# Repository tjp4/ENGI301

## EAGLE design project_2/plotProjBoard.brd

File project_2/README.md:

README

Project 02 contains the board and schematics for the plotter project made in project 01.

plotProjBoard.brd is the final version of the PCB, and uses the PocketBeagle, 2 DRV8833s, a 2.1mm Power Jack, and and a 3 pin 90 deg header. 

Associated documents are contained in the docs folder, including the BOM, gerber views, proposal, and schematic pdf.

-Tyler Pitts, ENGI301

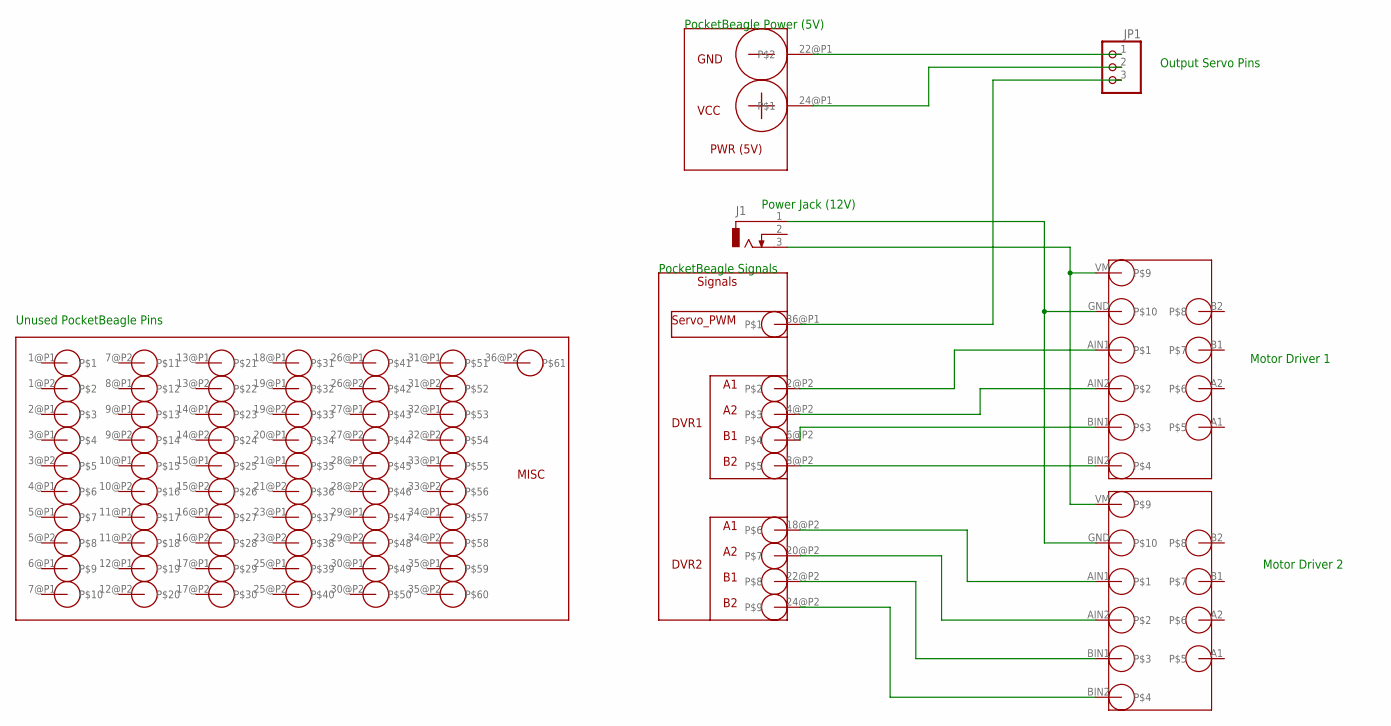
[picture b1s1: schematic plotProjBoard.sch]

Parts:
J1: DCJ0303
JP1: SERVO/90; 1X03/90
U$1, U$3: DRV8833
U$2: POCKETBEAGLE

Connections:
unnamed: U$1.AIN1, U$2.2@P2
unnamed: U$1.AIN2, U$2.4@P2
unnamed: U$1.BIN1, U$2.6@P2
unnamed: U$1.BIN2, U$2.8@P2
unnamed: U$2.18@P2, U$3.AIN1
unnamed: U$2.20@P2, U$3.AIN2
unnamed: U$2.22@P2, U$3.BIN1
unnamed: U$2.24@P2, U$3.BIN2
unnamed: JP1.3, U$2.36@P1
unnamed: JP1.2, U$2.24@P1
unnamed: JP1.1, U$2.22@P1
unnamed: J1.1, U$1.GND, U$3.GND
unnamed: J1.3, U$1.VM, U$3.VM

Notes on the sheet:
Unused PocketBeagle Pins
PocketBeagle Power (5V)
Power Jack (12V)
PocketBeagle Signals
Motor Driver 1
Motor Driver 2
Output Servo Pins

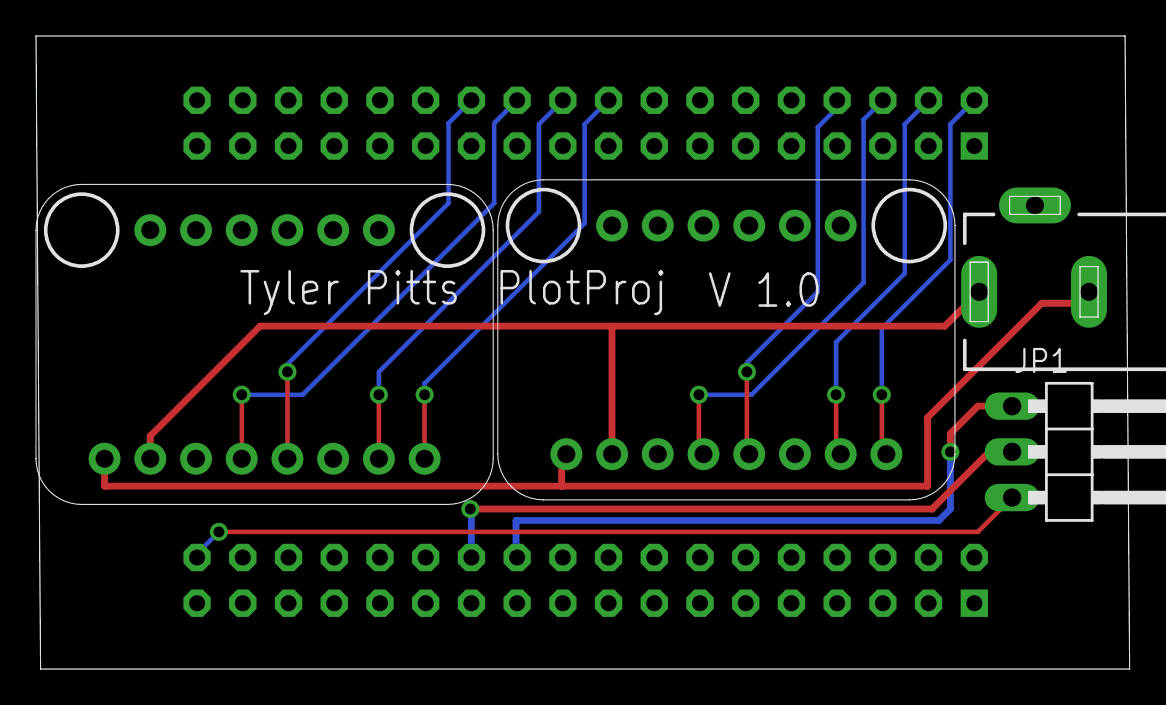
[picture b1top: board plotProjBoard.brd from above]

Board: 2 copper layers, 60.8 x 35.2 mm, 5 parts (1 on the bottom side), 13 nets.

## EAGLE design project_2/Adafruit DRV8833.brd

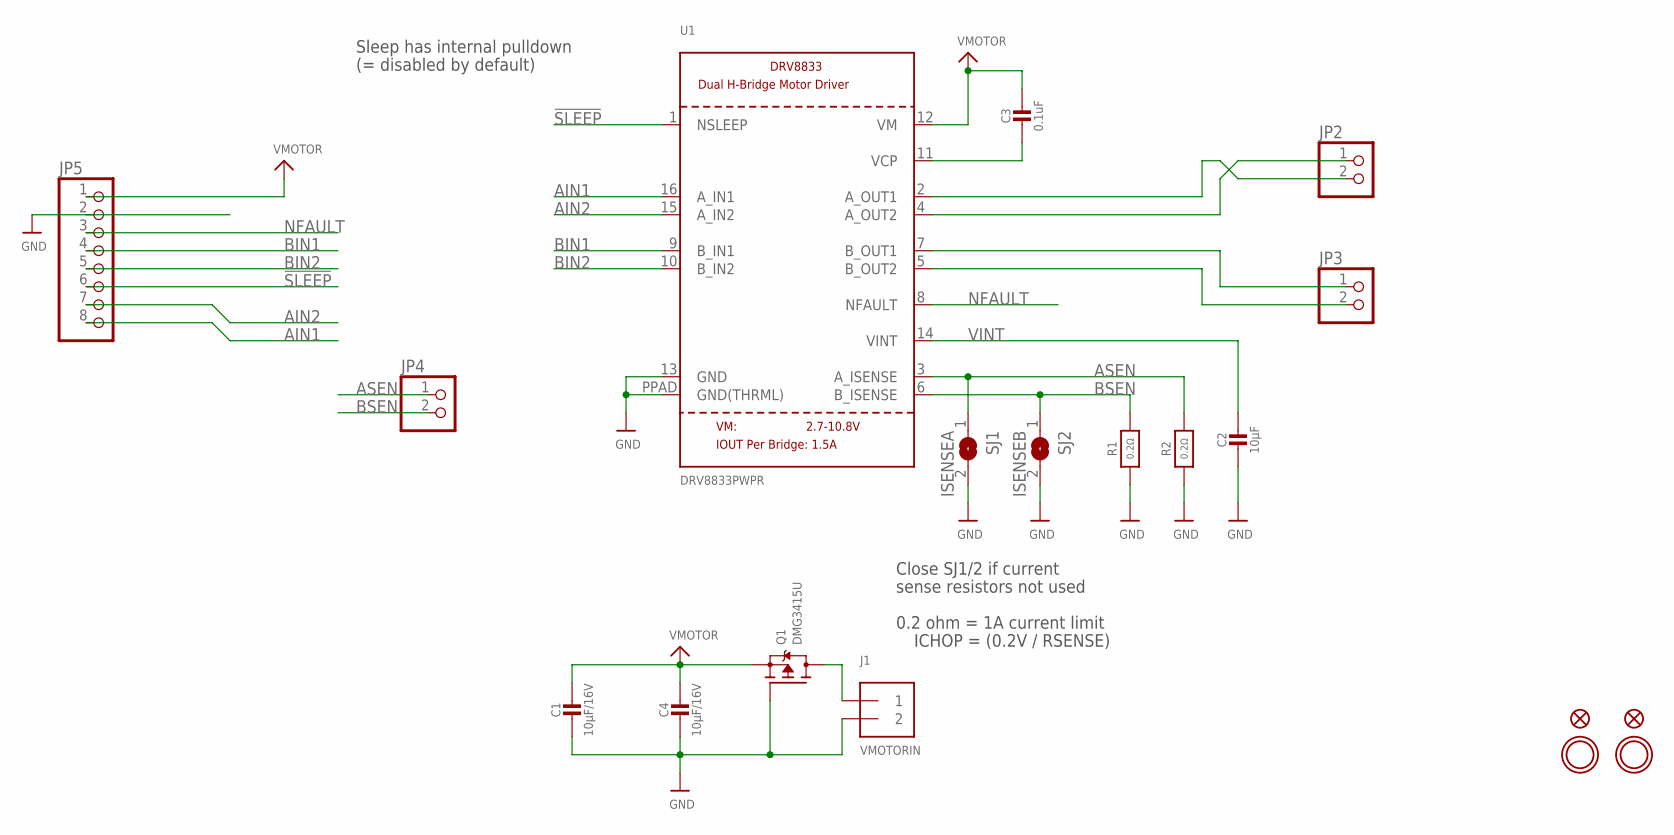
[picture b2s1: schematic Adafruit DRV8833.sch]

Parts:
C1, C4: 10µF/16V; 0805-NO
C2: 10µF; 0805-NO
C3: 0.1uF; 0805-NO
FID1, FID2: FIDUCIAL""; FIDUCIAL_1MM
J1: VMOTORIN; TERMBLOCK_1X2-3.5MM
JP2, JP3, JP4: HEADER-1X2ROUND; 1X02_ROUND
JP5: HEADER-1X870MIL; 1X08_ROUND_70
Q1: DMG3415U; SOT23-WIDE
R1, R2: 0.2Ω; _1206
SJ1: ISENSEA; SOLDERJUMPER_ARROW_NOPASTE
SJ2: ISENSEB; SOLDERJUMPER_ARROW_NOPASTE
U1: DRV8833PWPR; HTSSOP16
U$13, U$14: MOUNTINGHOLE2.5; MOUNTINGHOLE_2.5_PLATED

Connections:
!SLEEP: JP5.6, U1.1 (NSLEEP)
AIN1: JP5.8, U1.16 (A_IN1)
AIN2: JP5.7, U1.15 (A_IN2)
AOUT1: JP2.2, U1.2 (A_OUT1)
AOUT2: JP2.1, U1.4 (A_OUT2)
ASEN: JP4.1, R2.2, SJ1.1, U1.3 (A_ISENSE)
BIN1: JP5.4, U1.9 (B_IN1)
BIN2: JP5.5, U1.10 (B_IN2)
BOUT1: JP3.1, U1.7 (B_OUT1)
BOUT2: JP3.2, U1.5 (B_OUT2)
BSEN: JP4.2, R1.2, SJ2.1, U1.6 (B_ISENSE)
GND: C1.2, C2.2, C4.2, J1.2, JP5.2, Q1.1 (G), R1.1, R2.1, SJ1.2, SJ2.2, U1.13 (GND), U1.PPAD (GND(THRML))
unnamed: C3.2, U1.11 (VCP)
NFAULT: JP5.3, U1.8 (NFAULT)
PWRIN: J1.1, Q1.3 (D)
VINT: C2.1, U1.14 (VINT)
VMOTOR: C1.1, C3.1, C4.1, JP5.1, Q1.2 (S), U1.12 (VM)

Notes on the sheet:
Close SJ1/2 if current
sense resistors not used
0.2 ohm = 1A current limit
ICHOP = (0.2V / RSENSE)
Sleep has internal pulldown
(= disabled by default)

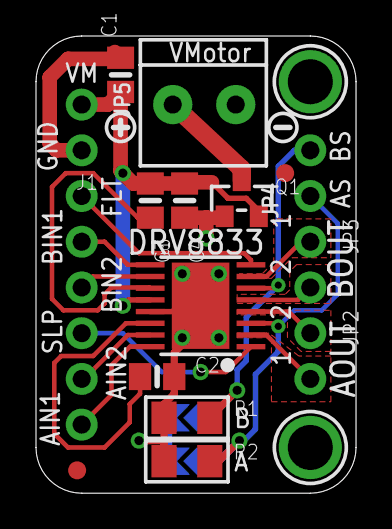
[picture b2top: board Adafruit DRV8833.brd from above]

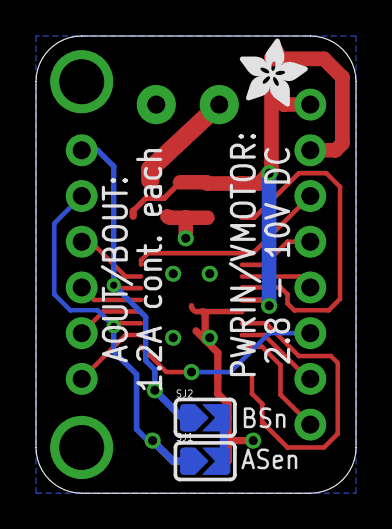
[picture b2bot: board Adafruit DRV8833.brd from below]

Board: 2 copper layers, 17.8 x 25.4 mm, 22 parts (3 on the bottom side), 17 nets.

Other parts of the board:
U$15: SYMBOL_PLUS
U$16: SYMBOL_MINUS
U$17: ADAFRUIT_3.5MM

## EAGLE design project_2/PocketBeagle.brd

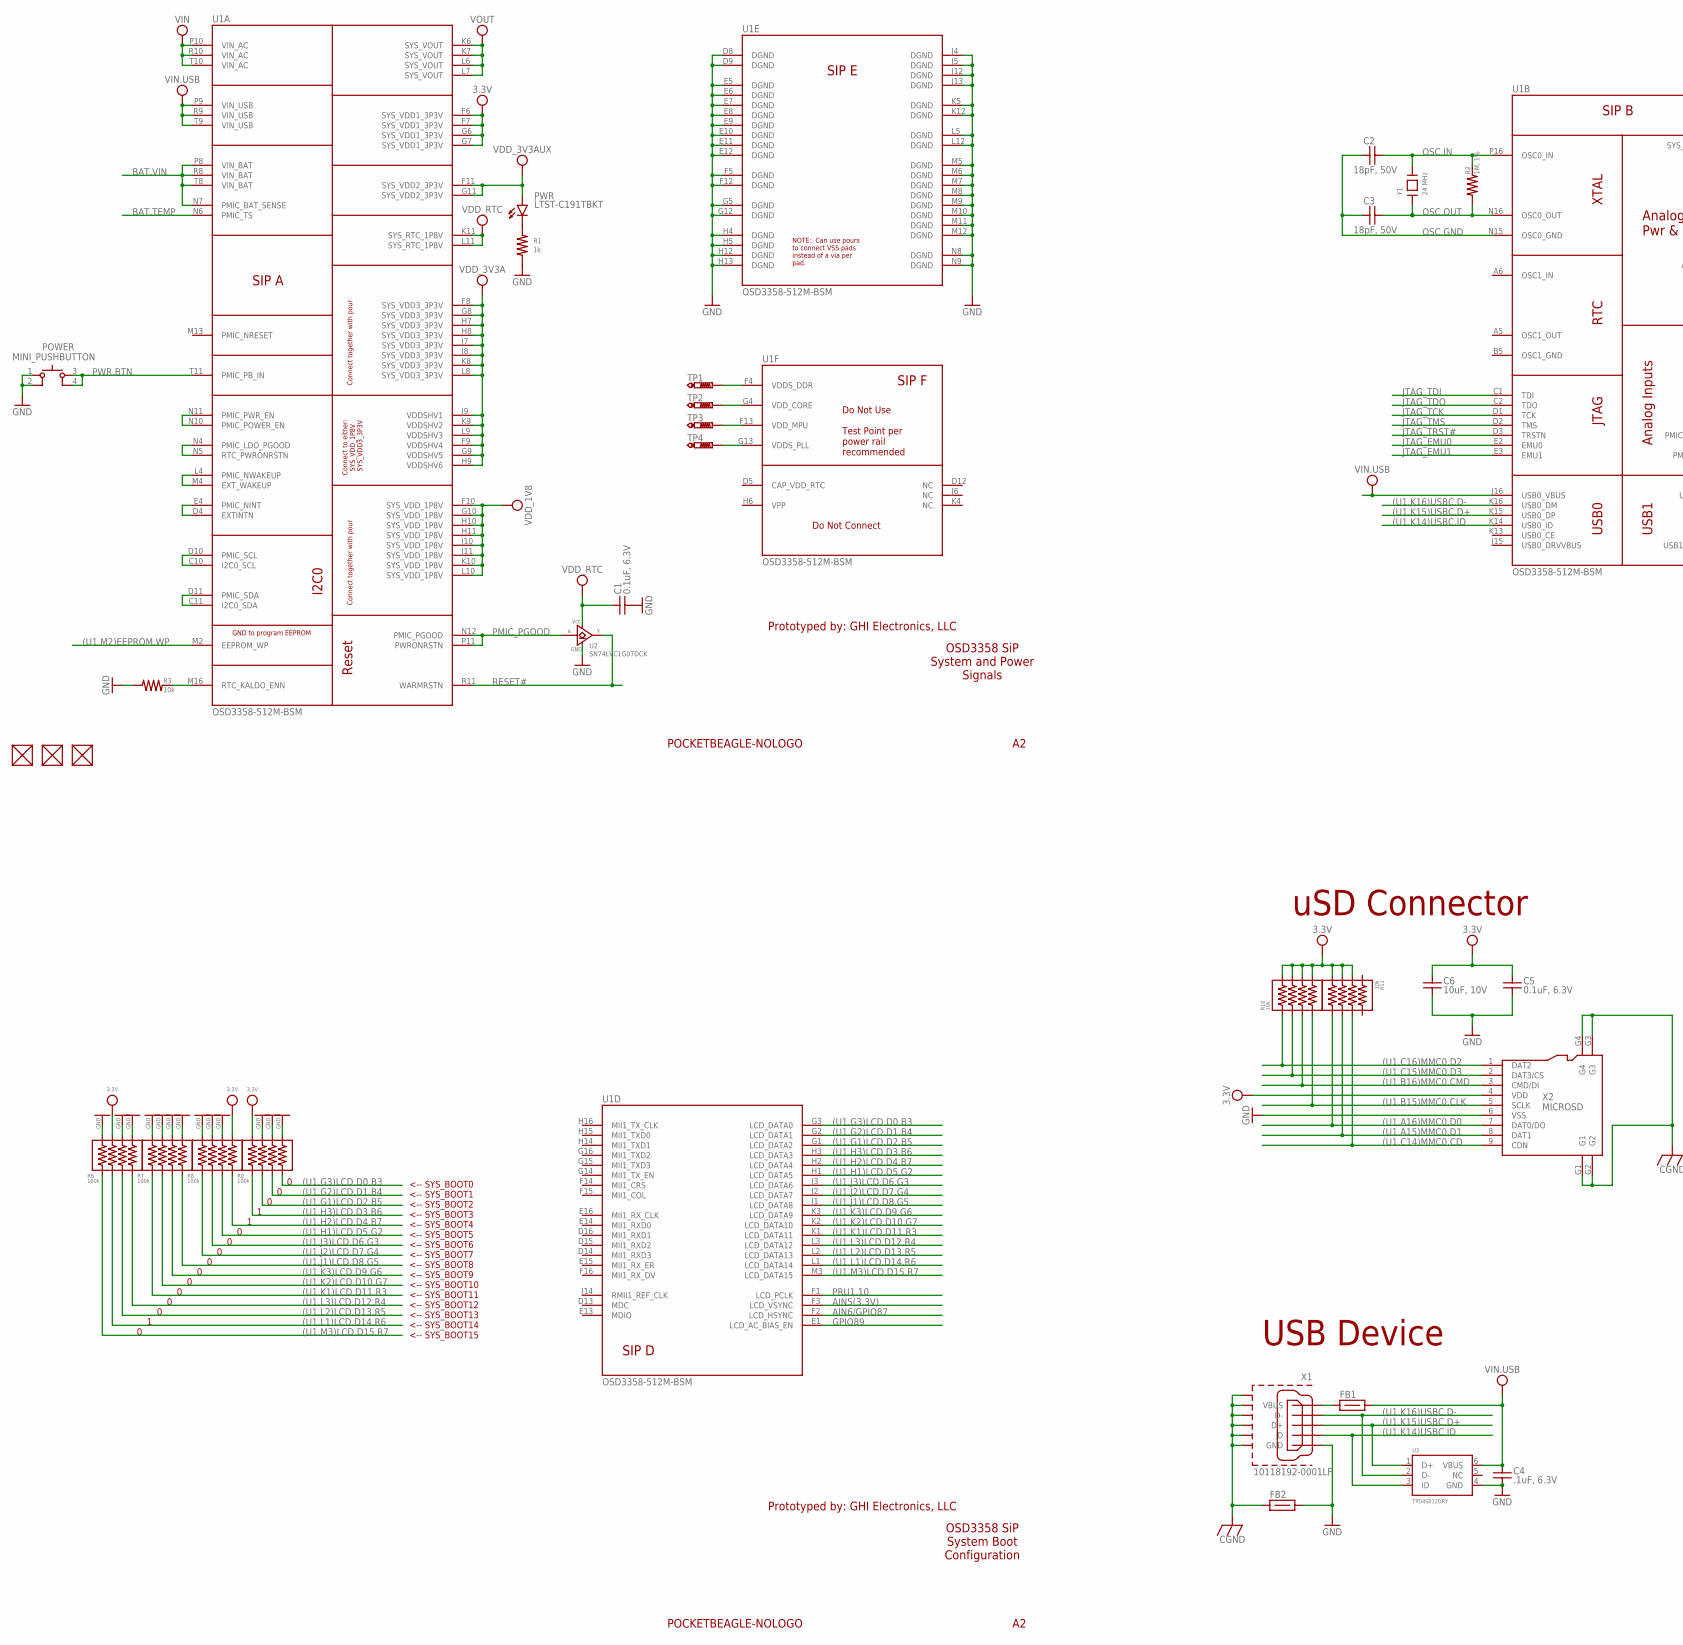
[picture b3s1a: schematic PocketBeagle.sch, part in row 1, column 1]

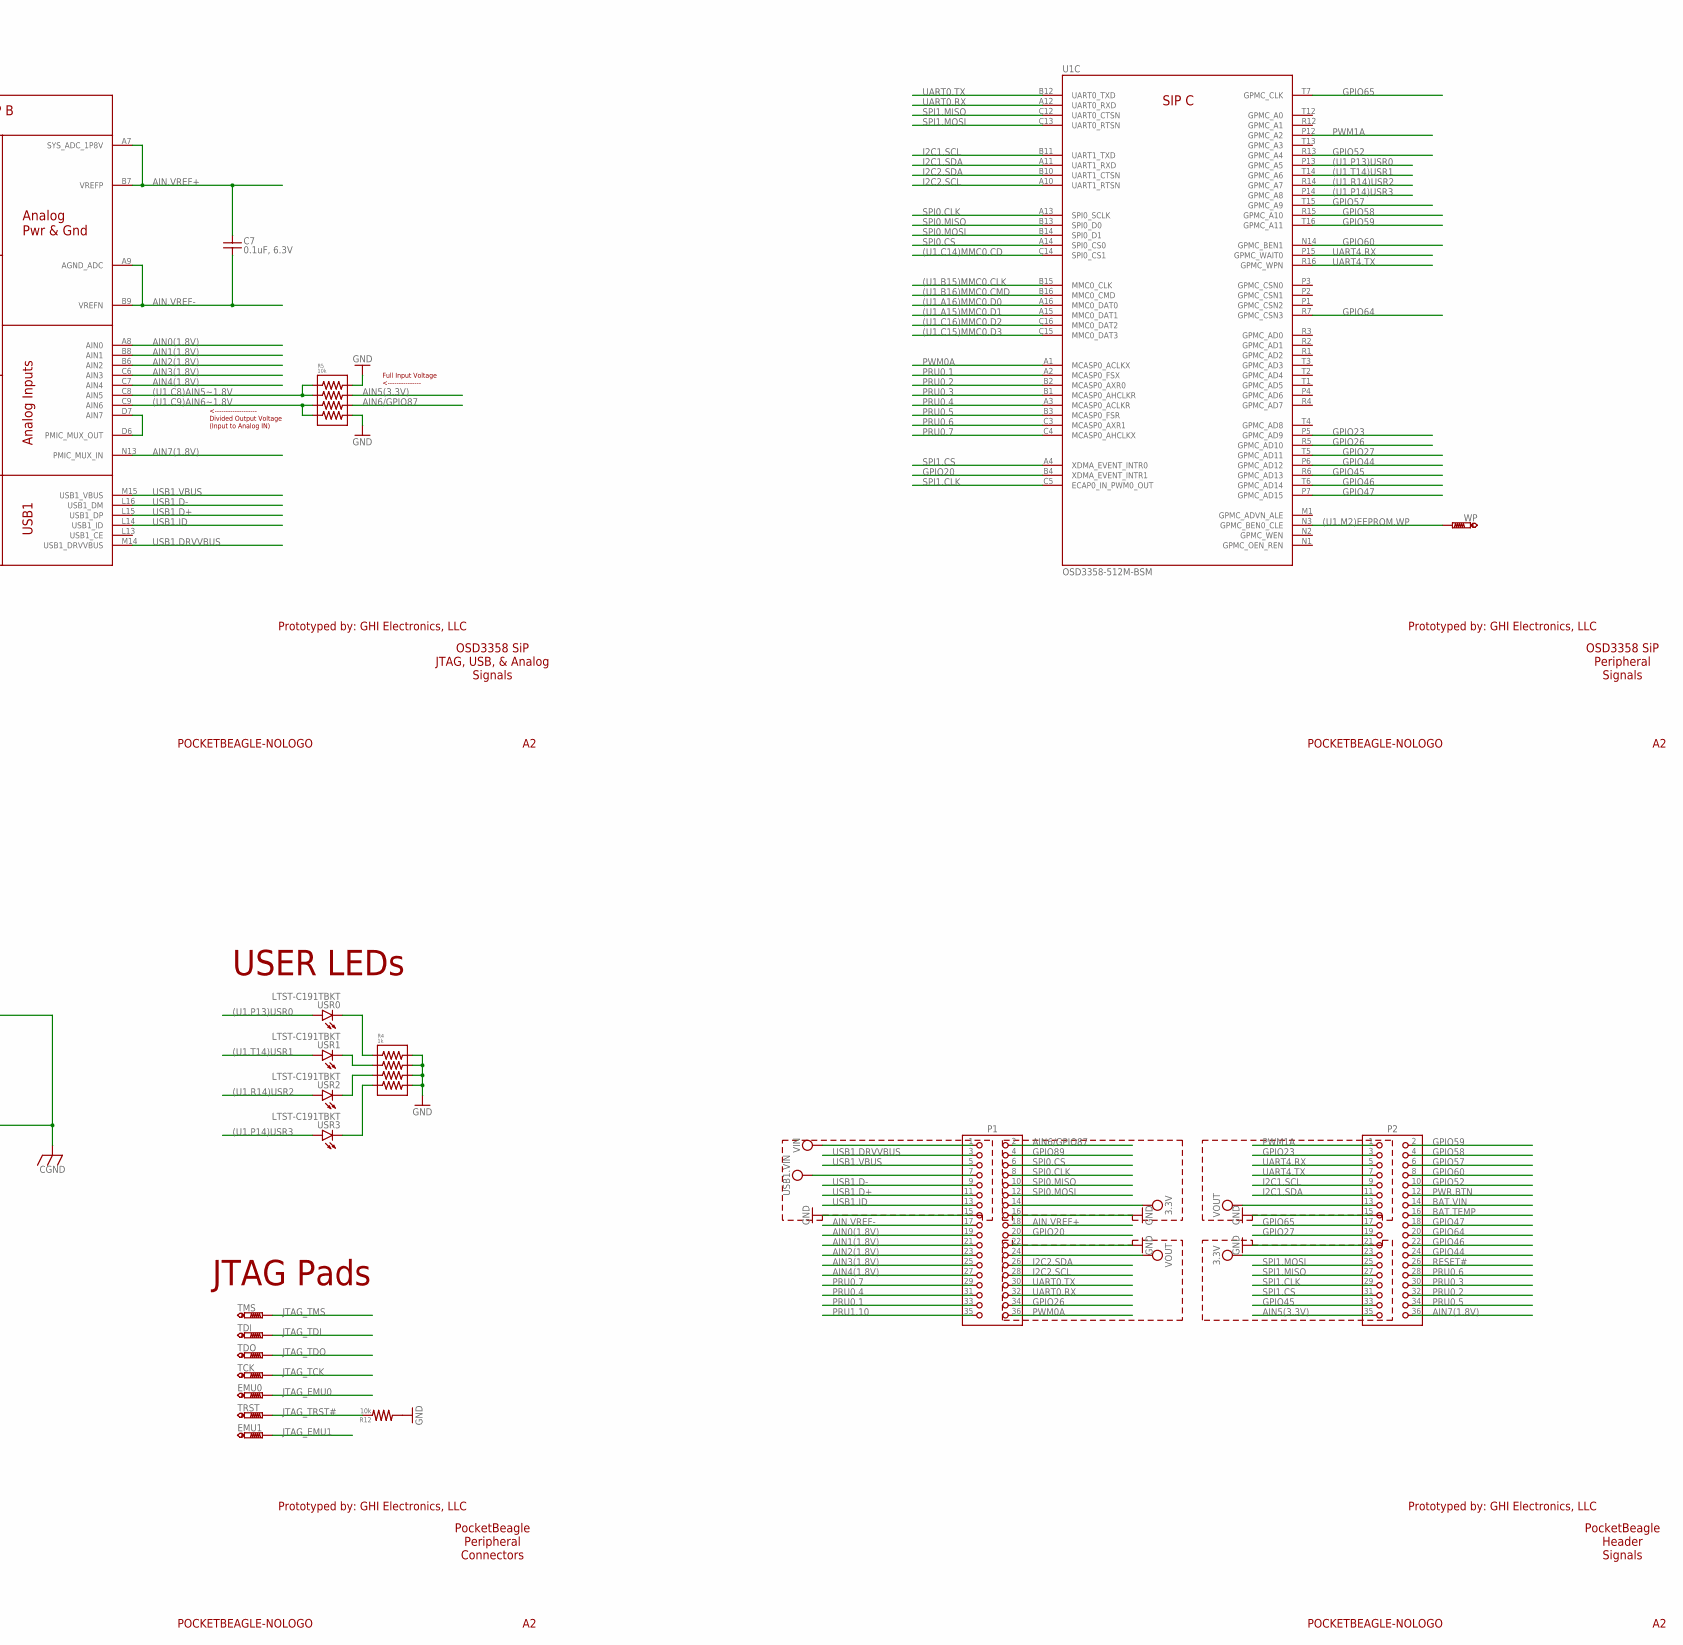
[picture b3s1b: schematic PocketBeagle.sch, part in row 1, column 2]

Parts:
C1, C5, C7: 0.1uF, 6.3V; 0402
C2, C3: 18pF, 50V; 0402
C4: .1uF, 6.3V; 0402
C6: 10uF, 10V; 0603
EMU0, EMU1: PTR1B1,27; B1,27
FB1, FB2: FB-(INCH)-0603; 0603
FUD1, FUD2, FUD3: FIDUCIAL; FIDUCIAL_40MIL
P1, P2: 2X18-(INCH)-0.1-TH-(35MIL-DIA)-W/O-SILK; TH-2X18-(35MIL-DIA)-W/O-SILK
POWER: MINI_PUSHBUTTON
PWR: LTST-C191TBKT; 0603-LED
R1: 1k; 0402
R2: 1M, 1%; 0402
R3, R12: 10k; 0402
R4: 1k; RN0804
R5, R10, R11: 10k; RN0804
R6, R7, R8, R9: 100k; RN0804
TCK: PTR1B1,27; B1,27
TDI: PTR1B1,27; B1,27
TDO: PTR1B1,27; B1,27
TMS: PTR1B1,27; B1,27
TP1, TP2, TP3, TP4: PTR1B1,27; B1,27
TRST: PTR1B1,27; B1,27
U1: OSD3358-512M-BSM; OSD335X-BGA-256
U2: SN74LVC1G07DCK; SC70(TI-DCK)
U3: TPD4S012DRY; SON-6(TI)-DRY
USR0, USR1, USR2, USR3: LTST-C191TBKT; 0603-LED
WP: PTR1B1,27; B1,27
X1: 10118192-0001LF; 10118192-0001LF(MICRO-USB-B-AMPHENOL-FCI)
X2: MICROSD
Y1: 24 MHz; CRYSTAL_5X3.2MM

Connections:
3.3V: C5.1, C6.1, P1.14, P2.23, R6.7, R8.5, R9.4, R10.5, R10.6, R10.7, R10.8, R11.2, R11.3, R11.4, U1.F6 (SYS_VDD1_3P3V), U1.F7 (SYS_VDD1_3P3V), U1.G6 (SYS_VDD1_3P3V), U1.G7 (SYS_VDD1_3P3V), X2.4 (VDD)
(U1.A15)MMC0.D1: R11.6, U1.A15 (MMC0_DAT1), X2.8 (DAT1)
(U1.A16)MMC0.D0: R11.5, U1.A16 (MMC0_DAT0), X2.7 (DAT0/DO)
(U1.B15)MMC0.CLK: R10.4, U1.B15 (MMC0_CLK), X2.5 (SCLK)
(U1.B16)MMC0.CMD: R10.3, U1.B16 (MMC0_CMD), X2.3 (CMD/DI)
(U1.C8)AIN5~1.8V: R5.1, R5.2, U1.C8 (AIN5)
(U1.C9)AIN6~1.8V: R5.3, R5.4, U1.C9 (AIN6)
(U1.C14)MMC0.CD: R11.7, U1.C14 (SPI0_CS1), X2.9 (CDN)
(U1.C15)MMC0.D3: R10.2, U1.C15 (MMC0_DAT3), X2.2 (DAT3/CS)
(U1.C16)MMC0.D2: R10.1, U1.C16 (MMC0_DAT2), X2.1 (DAT2)
(U1.G1)LCD.D2.B5: R9.6, U1.G1 (LCD_DATA2)
(U1.G2)LCD.D1.B4: R9.7, U1.G2 (LCD_DATA1)
(U1.G3)LCD.D0.B3: R9.8, U1.G3 (LCD_DATA0)
(U1.H1)LCD.D5.G2: R8.3, U1.H1 (LCD_DATA5)
(U1.H2)LCD.D4.B7: R8.4, U1.H2 (LCD_DATA4)
(U1.H3)LCD.D3.B6: R9.5, U1.H3 (LCD_DATA3)
(U1.J1)LCD.D8.G5: R7.4, U1.J1 (LCD_DATA8)
(U1.J2)LCD.D7.G4: R8.1, U1.J2 (LCD_DATA7)
(U1.J3)LCD.D6.G3: R8.2, U1.J3 (LCD_DATA6)
(U1.K1)LCD.D11.R3: R7.1, U1.K1 (LCD_DATA11)
(U1.K2)LCD.D10.G7: R7.2, U1.K2 (LCD_DATA10)
(U1.K3)LCD.D9.G6: R7.3, U1.K3 (LCD_DATA9)
(U1.K14)USBC.ID: U1.K14 (USB0_ID), U3.3 (ID), X1.ID
(U1.K15)USBC.D+: U1.K15 (USB0_DP), U3.1 (D+), X1.D+
(U1.K16)USBC.D-: U1.K16 (USB0_DM), U3.2 (D-), X1.D-
(U1.L1)LCD.D14.R6: R6.2, U1.L1 (LCD_DATA14)
(U1.L2)LCD.D13.R5: R6.3, U1.L2 (LCD_DATA13)
(U1.L3)LCD.D12.R4: R6.4, U1.L3 (LCD_DATA12)
(U1.M2)EEPROM.WP: U1.M2 (EEPROM_WP), U1.N3 (GPMC_BEN0_CLE), WP.TP
(U1.M3)LCD.D15.R7: R6.1, U1.M3 (LCD_DATA15)
(U1.P13)USR0: U1.P13 (GPMC_A5), USR0.A
(U1.P14)USR3: U1.P14 (GPMC_A8), USR3.A
(U1.R14)USR2: U1.R14 (GPMC_A7), USR2.A
(U1.T14)USR1: U1.T14 (GPMC_A6), USR1.A
AIN0(1.8V): P1.19, U1.A8 (AIN0)
AIN1(1.8V): P1.21, U1.B8 (AIN1)
AIN2(1.8V): P1.23, U1.B6 (AIN2)
AIN3(1.8V): P1.25, U1.C6 (AIN3)
AIN4(1.8V): P1.27, U1.C7 (AIN4)
AIN5(3.3V): P2.35, R5.7, U1.F3 (LCD_VSYNC)
AIN6/GPIO87: P1.2, R5.6, U1.F2 (LCD_HSYNC)
AIN7(1.8V): P2.36, U1.N13 (PMIC_MUX_IN)
AIN.VREF+: C7.1, P1.18, U1.A7 (SYS_ADC_1P8V), U1.B7 (VREFP)
AIN.VREF-: C7.2, P1.17, U1.A9 (AGND_ADC), U1.B9 (VREFN)
BAT.TEMP: P2.16, U1.N6 (PMIC_TS)
BAT.VIN: P2.14, U1.N7 (PMIC_BAT_SENSE), U1.P8 (VIN_BAT), U1.R8 (VIN_BAT), U1.T8 (VIN_BAT)
CGND: FB2.1, X1.CGND1 (SGND1), X1.CGND2 (SGND2), X1.CGND3 (SGND3), X1.CGND4 (SGND4), X1.CGND5 (SGND5), X1.CGND6 (SGND6), X2.G1, X2.G2, X2.G3, X2.G4
GND: C1.2, C4.2, C5.2, C6.2, FB2.2, P1.15, P1.16, P1.22, P2.15, P2.21, POWER.1, POWER.2, R1.1, R3.1, R4.5, R4.6, R4.7, R4.8, R5.5, R5.8, R6.5, R6.6, R6.8, R7.5, R7.6, R7.7, R7.8, R8.6, R8.7, R8.8, R9.1, R9.2, R9.3, R12.1, U1.D8 (DGND), U1.D9 (DGND), U1.E5 (DGND), U1.E6 (DGND), U1.E7 (DGND), U1.E8 (DGND), U1.E9 (DGND), U1.E10 (DGND), U1.E11 (DGND), U1.E12 (DGND), U1.F5 (DGND), U1.F12 (DGND), U1.G5 (DGND), U1.G12 (DGND), U1.H4 (DGND), U1.H5 (DGND), U1.H12 (DGND), U1.H13 (DGND), U1.J4 (DGND), U1.J5 (DGND), U1.J12 (DGND), U1.J13 (DGND), U1.K5 (DGND), U1.K12 (DGND), U1.L5 (DGND), U1.L12 (DGND), U1.M5 (DGND), U1.M6 (DGND), U1.M7 (DGND), U1.M8 (DGND), U1.M9 (DGND), U1.M10 (DGND), U1.M11 (DGND), U1.M12 (DGND), U1.N8 (DGND), U1.N9 (DGND), U2.3 (GND), U3.4 (GND), X1.GND, X2.6 (VSS)
GPIO20: P1.20, U1.B4 (XDMA_EVENT_INTR1)
GPIO23: P2.3, U1.P5 (GPMC_AD9)
GPIO26: P1.34, U1.R5 (GPMC_AD10)
GPIO27: P2.19, U1.T5 (GPMC_AD11)
GPIO44: P2.24, U1.P6 (GPMC_AD12)
GPIO45: P2.33, U1.R6 (GPMC_AD13)
GPIO46: P2.22, U1.T6 (GPMC_AD14)
GPIO47: P2.18, U1.P7 (GPMC_AD15)
GPIO52: P2.10, U1.R13 (GPMC_A4)
GPIO57: P2.6, U1.T15 (GPMC_A9)
GPIO58: P2.4, U1.R15 (GPMC_A10)
GPIO59: P2.2, U1.T16 (GPMC_A11)
GPIO60: P2.8, U1.N14 (GPMC_BEN1)
GPIO64: P2.20, U1.R7 (GPMC_CSN3)
GPIO65: P2.17, U1.T7 (GPMC_CLK)
GPIO89: P1.4, U1.E1 (LCD_AC_BIAS_EN)
I2C1.SCL: P2.9, U1.B11 (UART1_TXD)
I2C1.SDA: P2.11, U1.A11 (UART1_RXD)
I2C2.SCL: P1.28, U1.A10 (UART1_RTSN)
I2C2.SDA: P1.26, U1.B10 (UART1_CTSN)
JTAG_EMU0: EMU0.TP, U1.E2 (EMU0)
JTAG_EMU1: EMU1.TP, U1.E3 (EMU1)
JTAG_TCK: TCK.TP, U1.D1 (TCK)
JTAG_TDI: TDI.TP, U1.C1 (TDI)
JTAG_TDO: TDO.TP, U1.C2 (TDO)
JTAG_TMS: TMS.TP, U1.D2 (TMS)
JTAG_TRST#: R12.2, TRST.TP, U1.D3 (TRSTN)
unnamed: R4.3, USR2.K
unnamed: R4.4, USR3.K
unnamed: PWR.K, R1.2
unnamed: R4.2, USR1.K
unnamed: R4.1, USR0.K
unnamed: TP1.TP, U1.F4 (VDDS_DDR)
unnamed: TP2.TP, U1.G4 (VDD_CORE)
unnamed: TP3.TP, U1.F13 (VDD_MPU)
unnamed: TP4.TP, U1.G13 (VDDS_PLL)
unnamed: U1.D6 (PMIC_MUX_OUT), U1.D7 (AIN7)
unnamed: R3.2, U1.M16 (RTC_KALDO_ENN)
unnamed: U1.N4 (PMIC_LDO_PGOOD), U1.N5 (RTC_PWRONRSTN)
unnamed: U1.L4 (PMIC_NWAKEUP), U1.M4 (EXT_WAKEUP)
unnamed: U1.D4 (EXTINTN), U1.E4 (PMIC_NINT)
unnamed: U1.N10 (PMIC_POWER_EN), U1.N11 (PMIC_PWR_EN)
unnamed: U1.C11 (I2C0_SDA), U1.D11 (PMIC_SDA)
unnamed: U1.C10 (I2C0_SCL), U1.D10 (PMIC_SCL)
OSC.GND: C2.1, C3.1, U1.N15 (OSC0_GND)
OSC.IN: C2.2, R2.2, U1.P16 (OSC0_IN), Y1.2
OSC.OUT: C3.2, R2.1, U1.N16 (OSC0_OUT), Y1.1
PMIC_PGOOD: U1.N12 (PMIC_PGOOD), U1.P11 (PWRONRSTN), U2.2 (A)
PRU0.1: P1.33, U1.A2 (MCASP0_FSX)
PRU0.2: P2.32, U1.B2 (MCASP0_AXR0)
PRU0.3: P2.30, U1.B1 (MCASP0_AHCLKR)
PRU0.4: P1.31, U1.A3 (MCASP0_ACLKR)
PRU0.5: P2.34, U1.B3 (MCASP0_FSR)
PRU0.6: P2.28, U1.C3 (MCASP0_AXR1)
PRU0.7: P1.29, U1.C4 (MCASP0_AHCLKX)
PRU1.10: P1.35, U1.F1 (LCD_PCLK)
PWM0A: P1.36, U1.A1 (MCASP0_ACLKX)
PWM1A: P2.1, U1.P12 (GPMC_A2)
PWR.BTN: P2.12, POWER.3, POWER.4, U1.T11 (PMIC_PB_IN)
RESET#: P2.26, U1.R11 (WARMRSTN), U2.4 (Y)
SPI0.CLK: P1.8, U1.A13 (SPI0_SCLK)
SPI0.CS: P1.6, U1.A14 (SPI0_CS0)
SPI0.MISO: P1.10, U1.B13 (SPI0_D0)
SPI0.MOSI: P1.12, U1.B14 (SPI0_D1)
SPI1.CLK: P2.29, U1.C5 (ECAP0_IN_PWM0_OUT)
SPI1.CS: P2.31, U1.A4 (XDMA_EVENT_INTR0)
SPI1.MISO: P2.27, U1.C12 (UART0_CTSN)
SPI1.MOSI: P2.25, U1.C13 (UART0_RTSN)
UART0.RX: P1.32, U1.A12 (UART0_RXD)
UART0.TX: P1.30, U1.B12 (UART0_TXD)
UART4.RX: P2.5, U1.P15 (GPMC_WAIT0)
UART4.TX: P2.7, U1.R16 (GPMC_WPN)
USB1.D+: P1.11, U1.L15 (USB1_DP)
USB1.D-: P1.9, U1.L16 (USB1_DM)
USB1.DRVVBUS: P1.3, U1.M14 (USB1_DRVVBUS)
USB1.ID: P1.13, U1.L14 (USB1_ID)
USB1.VBUS: P1.5, U1.M15 (USB1_VBUS)
VBUS.RAW: FB1.1, X1.VBUS
VDD_1V8: U1.F10 (SYS_VDD_1P8V), U1.G10 (SYS_VDD_1P8V), U1.H10 (SYS_VDD_1P8V), U1.H11 (SYS_VDD_1P8V), U1.J10 (SYS_VDD_1P8V), U1.J11 (SYS_VDD_1P8V), U1.K10 (SYS_VDD_1P8V), U1.L10 (SYS_VDD_1P8V)
VDD_3V3A: U1.F8 (SYS_VDD3_3P3V), U1.F9 (VDDSHV4), U1.G8 (SYS_VDD3_3P3V), U1.G9 (VDDSHV5), U1.H7 (SYS_VDD3_3P3V), U1.H8 (SYS_VDD3_3P3V), U1.H9 (VDDSHV6), U1.J7 (SYS_VDD3_3P3V), U1.J8 (SYS_VDD3_3P3V), U1.J9 (VDDSHV1), U1.K8 (SYS_VDD3_3P3V), U1.K9 (VDDSHV2), U1.L8 (SYS_VDD3_3P3V), U1.L9 (VDDSHV3)
VDD_3V3AUX: PWR.A, U1.F11 (SYS_VDD2_3P3V), U1.G11 (SYS_VDD2_3P3V)
VDD_RTC: C1.1, U1.K11 (SYS_RTC_1P8V), U1.L11 (SYS_RTC_1P8V), U2.5 (VCC)
VIN: P1.1, U1.P10 (VIN_AC), U1.R10 (VIN_AC), U1.T10 (VIN_AC)
VIN.USB: C4.1, FB1.2, P1.7, U1.J16 (USB0_VBUS), U1.P9 (VIN_USB), U1.R9 (VIN_USB), U1.T9 (VIN_USB), U3.6 (VBUS)
VOUT: P1.24, P2.13, U1.K6 (SYS_VOUT), U1.K7 (SYS_VOUT), U1.L6 (SYS_VOUT), U1.L7 (SYS_VOUT)

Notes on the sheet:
<-- SYS_BOOT0 <-- SYS_BOOT1 <-- SYS_BOOT2 <-- SYS_BOOT3 <-- SYS_BOOT4 <-- SYS_BOOT5 <-- SYS_BOOT6 <-- SYS_BOOT7 <-- SYS_BOOT8 <-- SYS_BOOT9 <-- SYS_BOOT10 <-- SYS_BOOT11 <-- SYS_BOOT12 <-- SYS_BOOT13 <-- SYS_BOOT14 <-- SYS_BOOT15
USB Device
USER LEDs
uSD Connector
OSD3358 SiP System and Power Signals
Prototyped by: GHI Electronics, LLC
POCKETBEAGLE-NOLOGO
Full Input Voltage <---------------
<------------------- Divided Output Voltage (Input to Analog IN)
OSD3358 SiP JTAG, USB, & Analog Signals
OSD3358 SiP Peripheral Signals
OSD3358 SiP System Boot Configuration
PocketBeagle Peripheral Connectors
PocketBeagle Header Signals
JTAG Pads

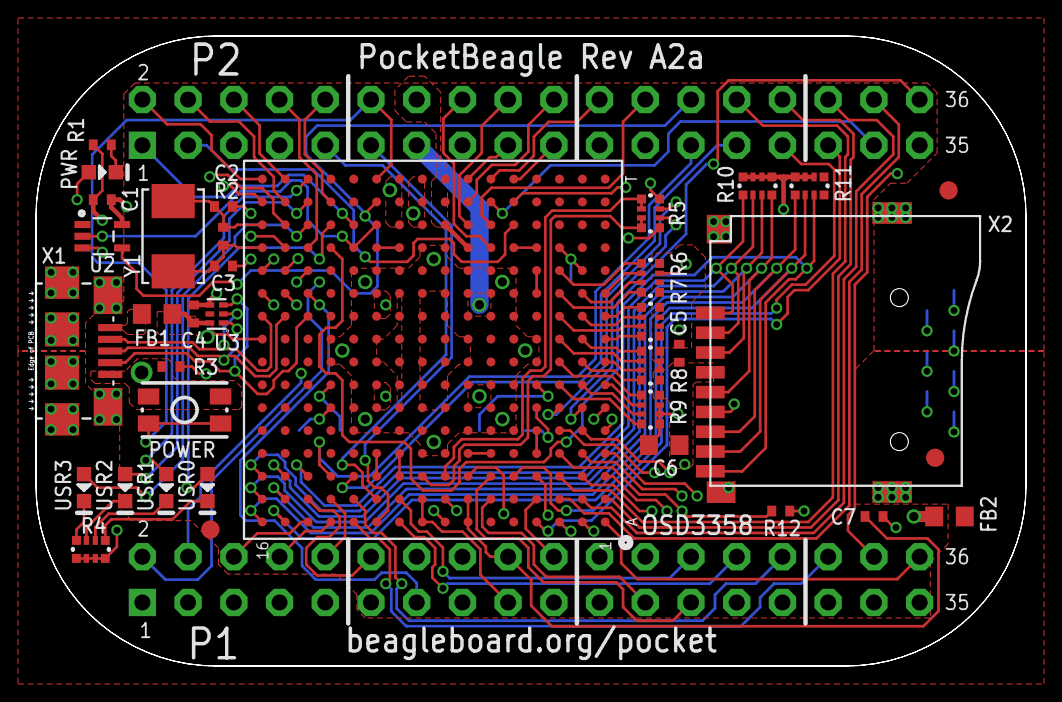
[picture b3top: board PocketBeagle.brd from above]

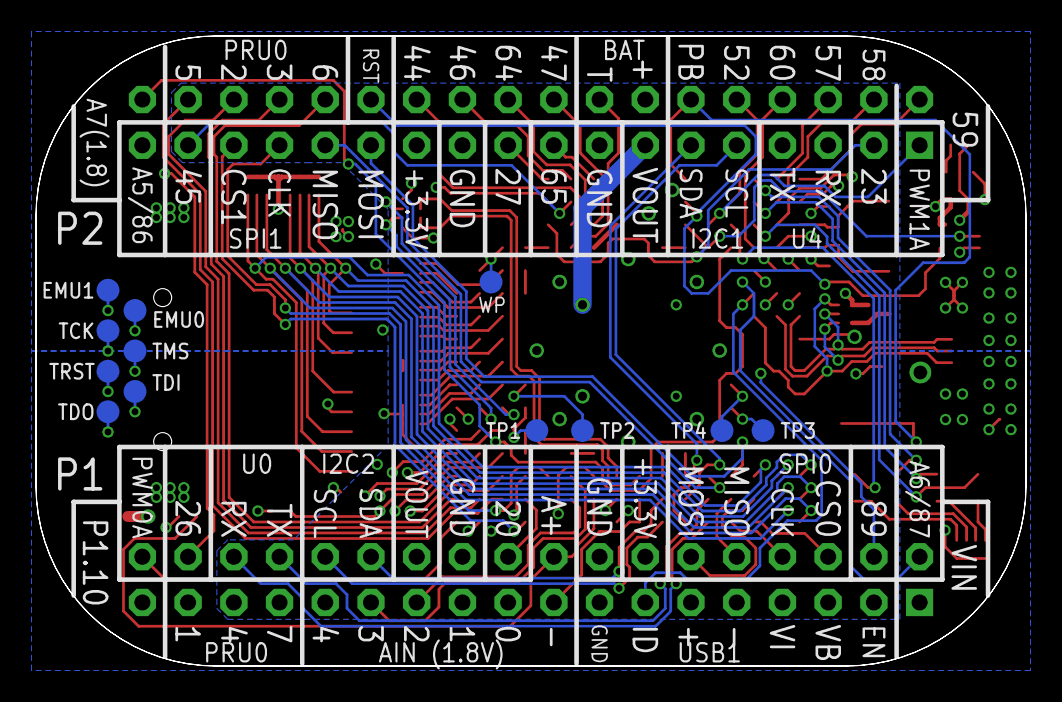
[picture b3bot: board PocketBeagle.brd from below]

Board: 4 copper layers, 55.0 x 35.0 mm, 50 parts (12 on the bottom side), 133 nets.

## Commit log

2022-02-15 assignment 4 work
2022-02-15 commiting assignment 3 to main, forgot to do earlier
2022-02-15 blink_USR3 added
2022-02-15 added comments, documentation and citations
2022-03-28 add proj
2022-03-28 comitting
2022-03-28 aaaaa
2022-03-28 a
    aaa
2022-03-30 aaa
    aaaaa
2022-03-31 code tested and works, stepper motors too weak / too high step size
2022-03-31 Create ENGI_301_CAD (3).zip
    add CAD files
2022-03-31 removed unnecessary file
2022-03-31 removed Unnecessary file, added autorun
2022-03-31 Added readme
2022-04-12 Project2
    Project2
2022-04-29 Project 02
    Project 02
